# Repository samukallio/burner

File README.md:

# burner
Programmers for legacy EEPROM and CPLD devices

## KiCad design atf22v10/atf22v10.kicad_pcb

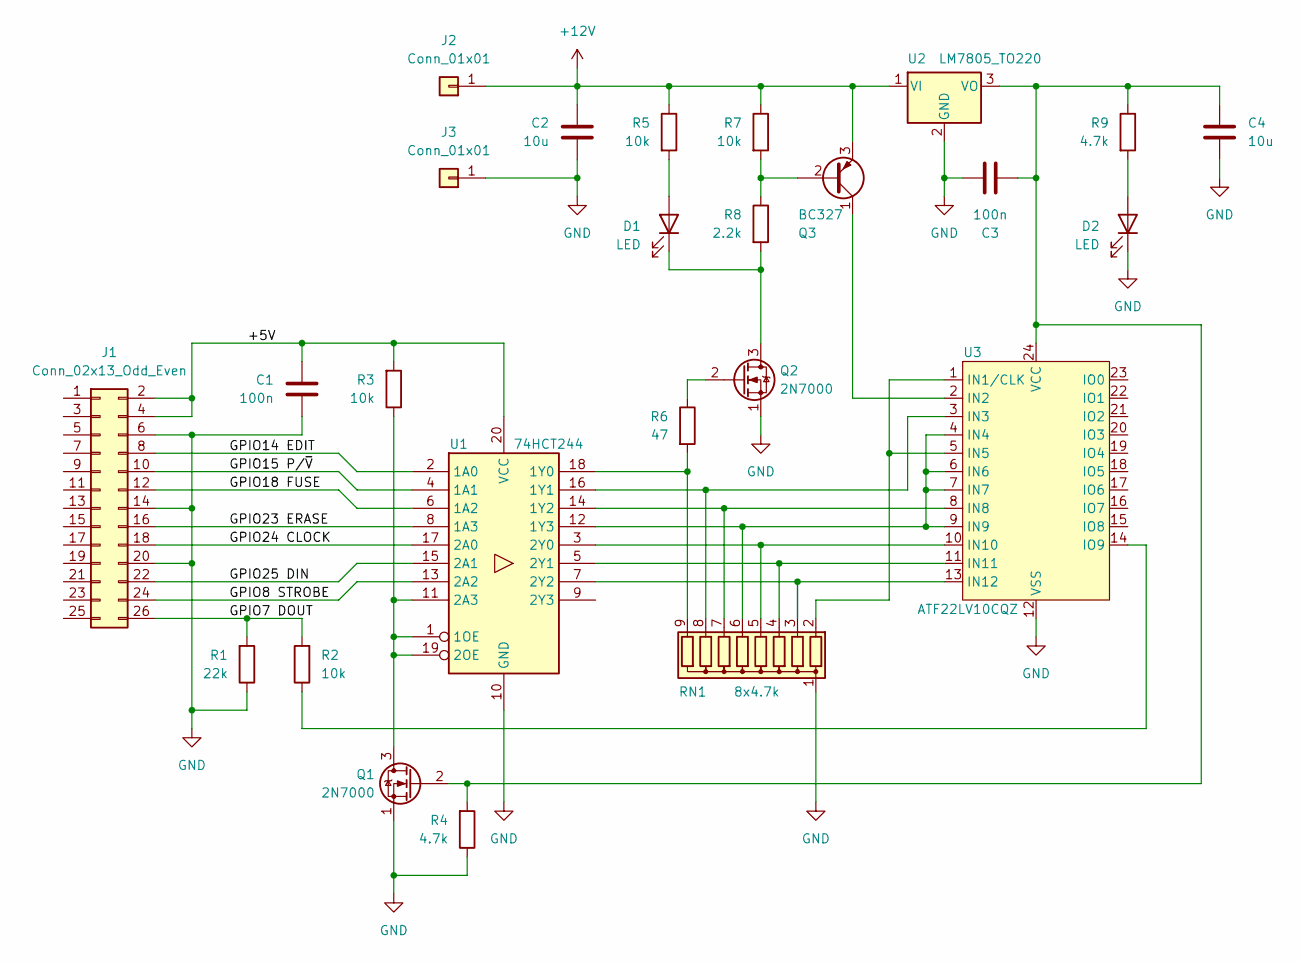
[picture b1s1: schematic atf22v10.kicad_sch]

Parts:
C1, C3: 100n; C_Disc_D3.4mm_W2.1mm_P2.50mm
C2, C4: 10u; CP_Radial_D5.0mm_P2.50mm
D1, D2: LED; LED_D3.0mm
J1: Conn_02x13_Odd_Even; PinHeader_2x13_P2.54mm_Vertical
J2, J3: Conn_01x01; Connector_Banana_THT
Q1, Q2: 2N7000; TO-92_Inline_Wide
Q3: BC327; TO-92_Inline_Wide
R1: 22k; R_Axial_DIN0207_L6.3mm_D2.5mm_P7.62mm_Horizontal
R2, R3, R5, R7: 10k; R_Axial_DIN0207_L6.3mm_D2.5mm_P7.62mm_Horizontal
R4, R9: 4.7k; R_Axial_DIN0207_L6.3mm_D2.5mm_P7.62mm_Horizontal
R6: 47; R_Axial_DIN0207_L6.3mm_D2.5mm_P7.62mm_Horizontal
R8: 2.2k; R_Axial_DIN0207_L6.3mm_D2.5mm_P7.62mm_Horizontal
RN1: 8x4.7k; R_Array_SIP9
U1: 74HCT244; DIP-20_W7.62mm_Socket
U2: LM7805_TO220; TO-220-3_Vertical
U3: ATF22LV10CQZ; DIP-24_W7.62mm_Socket

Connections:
+12V: C2.1, J2.1, Q3.3 (E), R5.1, R7.1, U2.1 (VI)
/+5V: C1.1, J1.2, J1.4, R3.2, U1.20 (VCC)
/GPIO7 DOUT: J1.26, R1.2, R2.2
/GPIO8 STROBE: J1.24, U1.13 (2A2)
/GPIO14 EDIT: J1.8, U1.2 (1A0)
/GPIO15 P/~V: J1.10, U1.4 (1A1)
/GPIO18 FUSE: J1.12, U1.6 (1A2)
/GPIO23 ERASE: J1.16, U1.8 (1A3)
/GPIO24 CLOCK: J1.18, U1.17 (2A0)
/GPIO25 DIN: J1.22, U1.15 (2A1)
GND: C1.2, C2.2, C3.2, C4.2, D2.1 (K), J1.6, J1.14, J1.20, J3.1, Q1.1 (S), Q2.1 (S), R1.1, R4.1, RN1.1 (common), U1.10 (GND), U2.2 (GND), U3.12 (VSS)
unnamed: D1.2 (A), R5.2
unnamed: D1.1 (K), Q2.3 (D), R8.2
unnamed: D2.2 (A), R9.2
unnamed: Q1.3 (D), R3.1, U1.1 (1OE), U1.11 (2A3), U1.19 (2OE)
unnamed: C3.1, C4.1, Q1.2 (G), R4.2, R9.1, U2.3 (VO), U3.24 (VCC)
unnamed: Q2.2 (G), R6.1
unnamed: Q3.2 (B), R7.2, R8.1
unnamed: Q3.1 (C), U3.2 (IN2)
unnamed: RN1.2 (R1), U3.1 (IN1/CLK), U3.5 (IN5)
unnamed: RN1.3 (R2), U1.7 (2Y2), U3.13 (IN12)
unnamed: RN1.4 (R3), U1.5 (2Y1), U3.11 (IN11)
unnamed: RN1.5 (R4), U1.3 (2Y0), U3.10 (IN10)
unnamed: RN1.6 (R5), U1.12 (1Y3), U3.4 (IN4), U3.6 (IN6), U3.7 (IN7), U3.9 (IN9)
unnamed: RN1.7 (R6), U1.14 (1Y2), U3.8 (IN8)
unnamed: RN1.8 (R7), U1.16 (1Y1), U3.3 (IN3)
unnamed: R6.2, RN1.9 (R8), U1.18 (1Y0)
unnamed: R2.1, U3.14 (IO9)

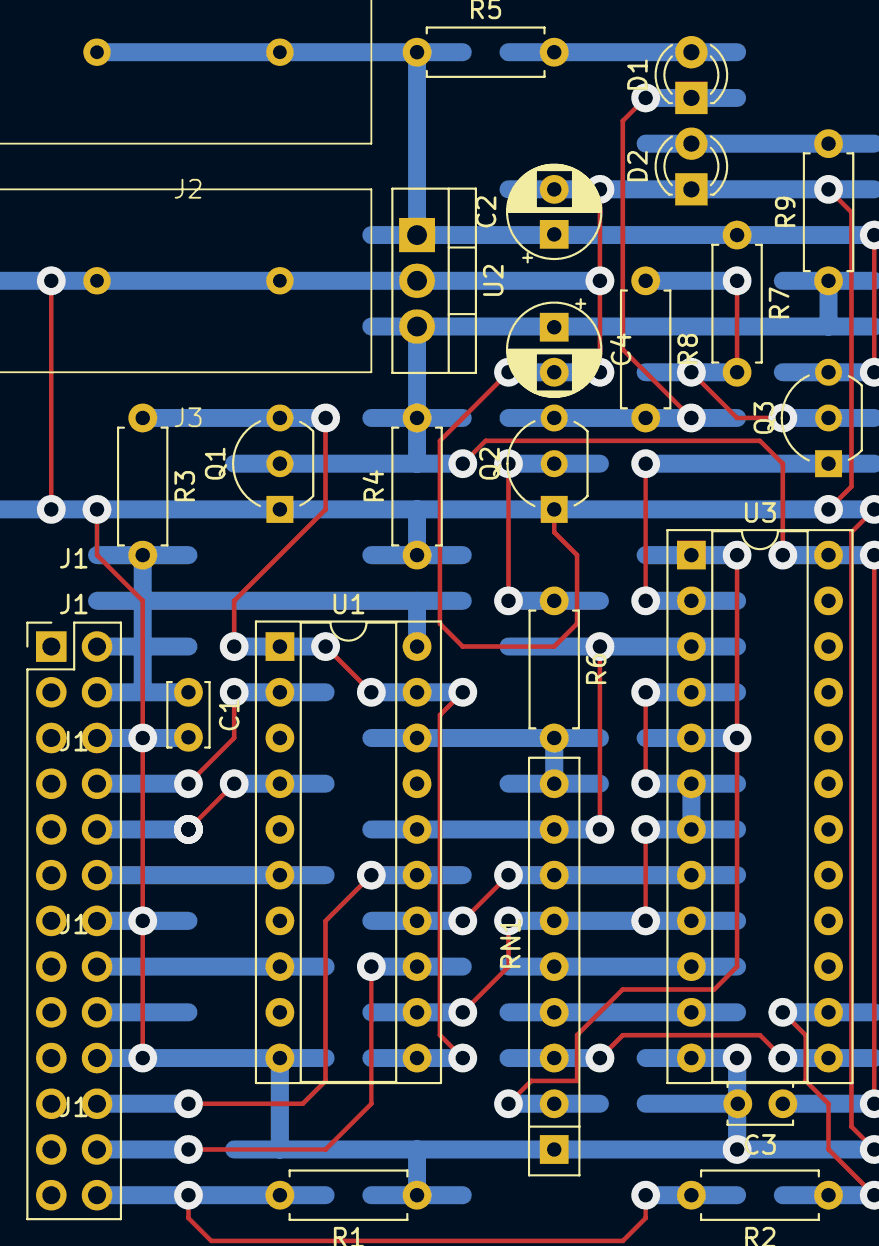
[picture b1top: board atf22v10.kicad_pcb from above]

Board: 2 copper layers, 25 parts (0 on the bottom side), 28 nets.

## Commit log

2024-02-26 Add ATF22V10 burner schematic and script
2024-02-26 Add KiCad lockfiles to .gitignore
2024-02-26 Schematic cleanup
